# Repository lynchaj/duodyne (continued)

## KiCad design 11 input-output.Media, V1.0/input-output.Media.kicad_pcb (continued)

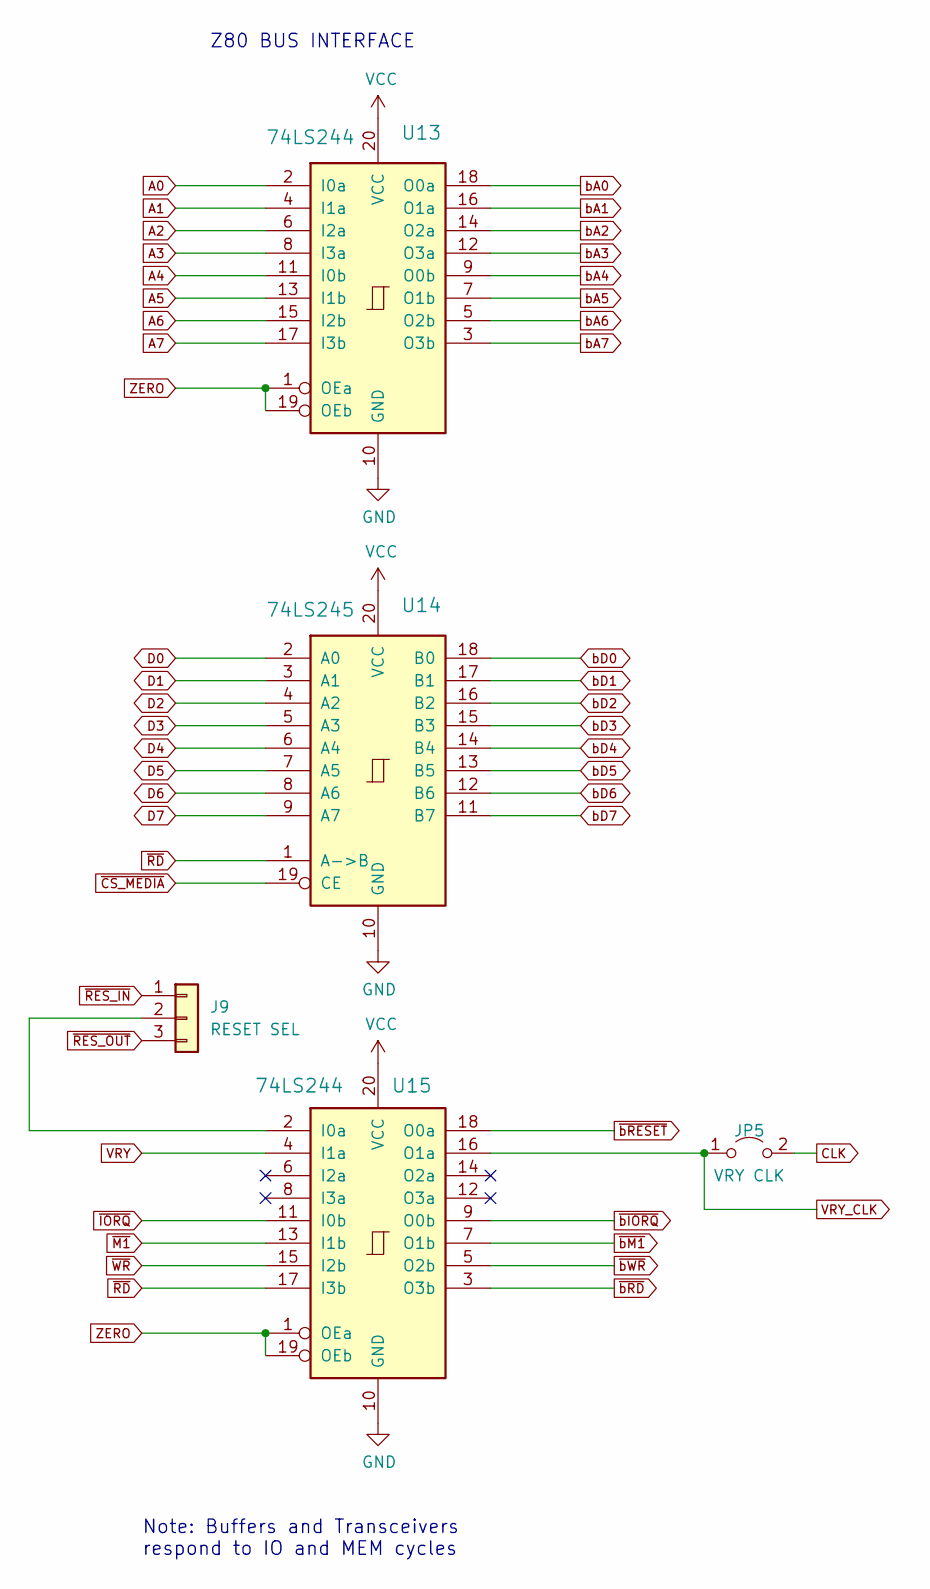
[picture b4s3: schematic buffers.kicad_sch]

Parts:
J9: RESET SEL; PinHeader_1x03_P2.54mm_Vertical
JP5: VRY CLK; PinHeader_1x02_P2.54mm_Vertical
U13, U15: 74LS244; DIP-20_W7.62mm
U14: 74LS245; DIP-20_W7.62mm

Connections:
A0: U13.2 (I0a); also elsewhere on the board
A1: U13.4 (I1a); also elsewhere on the board
A2: U13.6 (I2a); also elsewhere on the board
A3: U13.8 (I3a); also elsewhere on the board
A4: U13.11 (I0b); also elsewhere on the board
A5: U13.13 (I1b); also elsewhere on the board
A6: U13.15 (I2b); also elsewhere on the board
A7: U13.17 (I3b); also elsewhere on the board
CLK: JP5.2 (B); also elsewhere on the board
D0: U14.2 (A0); also elsewhere on the board
D1: U14.3 (A1); also elsewhere on the board
D2: U14.4 (A2); also elsewhere on the board
D3: U14.5 (A3); also elsewhere on the board
D4: U14.6 (A4); also elsewhere on the board
D5: U14.7 (A5); also elsewhere on the board
D6: U14.8 (A6); also elsewhere on the board
D7: U14.9 (A7); also elsewhere on the board
GND: U13.10 (GND), U14.10 (GND), U15.10 (GND); also elsewhere on the board
unnamed: J9.2, U15.2 (I0a)
VCC: U13.20 (VCC), U14.20 (VCC), U15.20 (VCC); also elsewhere on the board
VRY: U15.4 (I1a); also elsewhere on the board
VRY_CLK: JP5.1 (A), U15.16 (O1a); also elsewhere on the board
ZERO: U13.1 (OEa), U13.19 (OEb), U15.1 (OEa), U15.19 (OEb); also elsewhere on the board
bA0: U13.18 (O0a); also elsewhere on the board
bA1: U13.16 (O1a); also elsewhere on the board
bA2: U13.14 (O2a); also elsewhere on the board
bA3: U13.12 (O3a); also elsewhere on the board
bA4: U13.9 (O0b); also elsewhere on the board
bA5: U13.7 (O1b); also elsewhere on the board
bA6: U13.5 (O2b); also elsewhere on the board
bA7: U13.3 (O3b); also elsewhere on the board
bD0: U14.18 (B0); also elsewhere on the board
bD1: U14.17 (B1); also elsewhere on the board
bD2: U14.16 (B2); also elsewhere on the board
bD3: U14.15 (B3); also elsewhere on the board
bD4: U14.14 (B4); also elsewhere on the board
bD5: U14.13 (B5); also elsewhere on the board
bD6: U14.12 (B6); also elsewhere on the board
bD7: U14.11 (B7); also elsewhere on the board
~CS_MEDIA: U14.19 (CE); also elsewhere on the board
~IORQ: U15.11 (I0b); also elsewhere on the board
~M1: U15.13 (I1b); also elsewhere on the board
~RD: U14.1 (A->B), U15.17 (I3b); also elsewhere on the board
~RES_IN: J9.1; also elsewhere on the board
~RES_OUT: J9.3; also elsewhere on the board
~WR: U15.15 (I2b); also elsewhere on the board
~bIORQ: U15.9 (O0b); also elsewhere on the board
~bM1: U15.7 (O1b); also elsewhere on the board
~bRD: U15.3 (O3b); also elsewhere on the board
~bRESET: U15.18 (O0a); also elsewhere on the board
~bWR: U15.5 (O2b); also elsewhere on the board

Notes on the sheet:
Z80 BUS INTERFACE
Note: Buffers and Transceivers respond to IO and MEM cycles

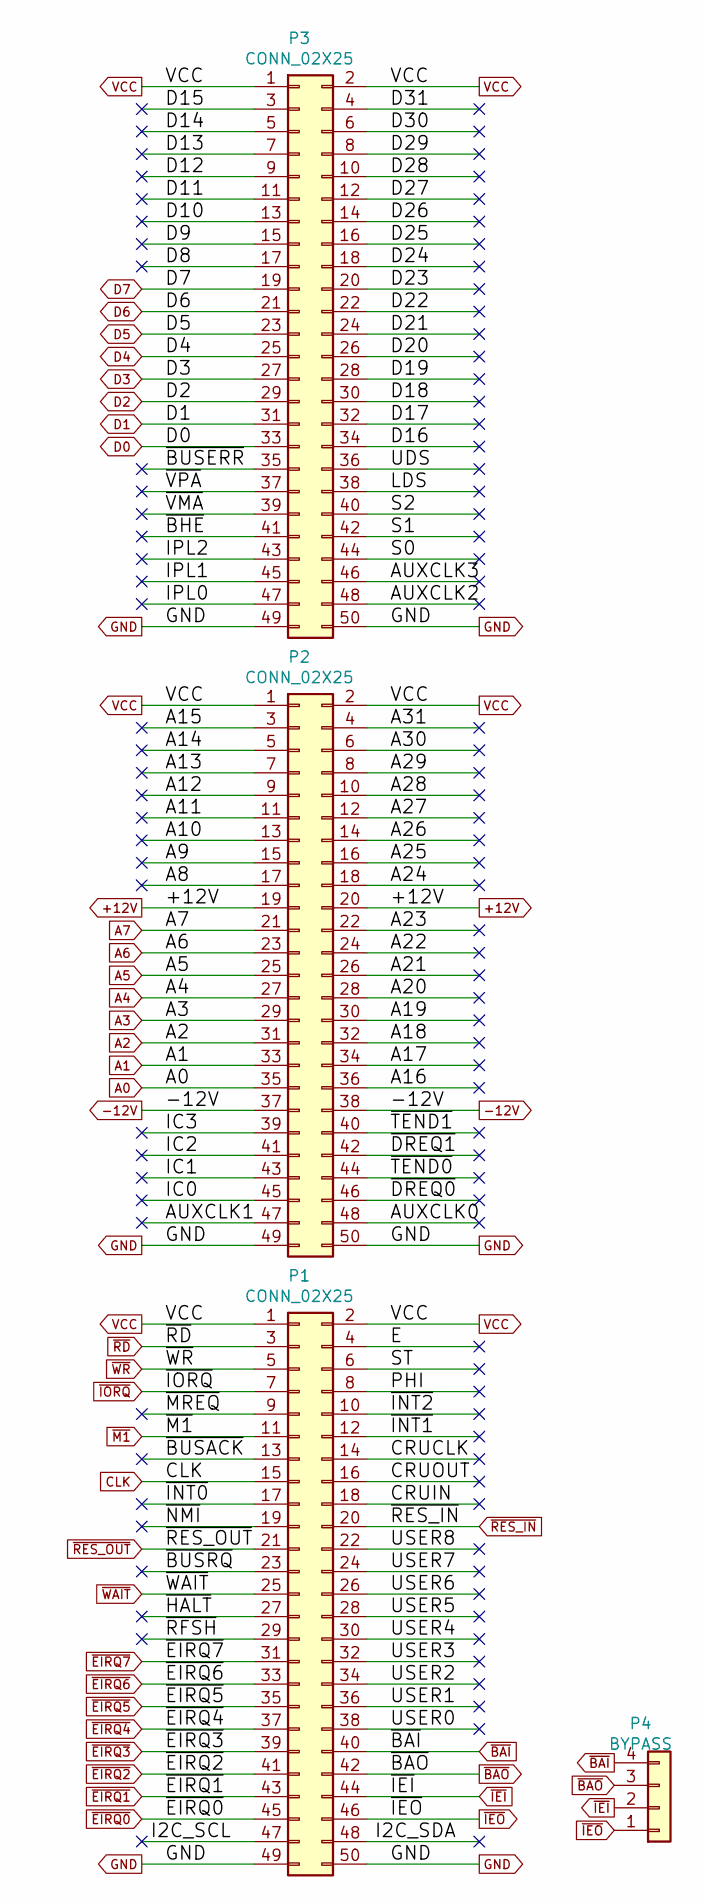
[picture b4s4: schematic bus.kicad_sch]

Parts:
P1, P2, P3: CONN_02X25; IDC-Header_2x25_P2.54mm_Horizontal
P4: BYPASS; PinHeader_1x04_P2.54mm_Vertical

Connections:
+12V: P2.19, P2.20; also elsewhere on the board
-12V: P2.37, P2.38
/bus/A8: P2.17
/bus/A9: P2.15
/bus/A10: P2.13
/bus/A11: P2.11
/bus/A12: P2.9
/bus/A13: P2.7
/bus/A14: P2.5
/bus/A15: P2.3
/bus/A16: P2.36
/bus/A17: P2.34
/bus/A18: P2.32
/bus/A19: P2.30
/bus/A20: P2.28
/bus/A21: P2.26
/bus/A22: P2.24
/bus/A23: P2.22
/bus/A24: P2.18
/bus/A25: P2.16
/bus/A26: P2.14
/bus/A27: P2.12
/bus/A28: P2.10
/bus/A29: P2.8
/bus/A30: P2.6
/bus/A31: P2.4
/bus/AUXCLK0: P2.48
/bus/AUXCLK1: P2.47
/bus/AUXCLK2: P3.48
/bus/AUXCLK3: P3.46
/bus/CRUCLK: P1.14
/bus/CRUIN: P1.18
/bus/CRUOUT: P1.16
/bus/D8: P3.17
/bus/D9: P3.15
/bus/D10: P3.13
/bus/D11: P3.11
/bus/D12: P3.9
/bus/D13: P3.7
/bus/D14: P3.5
/bus/D15: P3.3
/bus/D16: P3.34
/bus/D17: P3.32
/bus/D18: P3.30
/bus/D19: P3.28
/bus/D20: P3.26
/bus/D21: P3.24
/bus/D22: P3.22
/bus/D23: P3.20
/bus/D24: P3.18
/bus/D25: P3.16
/bus/D26: P3.14
/bus/D27: P3.12
/bus/D28: P3.10
/bus/D29: P3.8
/bus/D30: P3.6
/bus/D31: P3.4
/bus/E: P1.4
/bus/I2C_SCL: P1.47
/bus/I2C_SDA: P1.48
/bus/IC0: P2.45
/bus/IC1: P2.43
/bus/IC2: P2.41
/bus/IC3: P2.39
/bus/IPL0: P3.47
/bus/IPL1: P3.45
/bus/IPL2: P3.43
/bus/LDS: P3.38
/bus/PHI: P1.8
/bus/S0: P3.44
/bus/S1: P3.42
/bus/S2: P3.40
/bus/ST: P1.6
/bus/UDS: P3.36
/bus/USER0: P1.38
/bus/USER1: P1.36
/bus/USER2: P1.34
/bus/USER3: P1.32
/bus/USER4: P1.30
/bus/USER5: P1.28
/bus/USER6: P1.26
/bus/USER7: P1.24
/bus/USER8: P1.22
/bus/~BHE: P3.41
/bus/~BUSACK: P1.13
/bus/~BUSERR: P3.35
/bus/~BUSRQ: P1.23
/bus/~DREQ0: P2.46
/bus/~DREQ1: P2.42
/bus/~HALT: P1.27
/bus/~INT0: P1.17
/bus/~INT1: P1.12
/bus/~INT2: P1.10
/bus/~MREQ: P1.9
/bus/~NMI: P1.19
/bus/~RFSH: P1.29
/bus/~TEND0: P2.44
/bus/~TEND1: P2.40
/bus/~VMA: P3.39
/bus/~VPA: P3.37
A0: P2.35; also elsewhere on the board
A1: P2.33; also elsewhere on the board
A2: P2.31; also elsewhere on the board
A3: P2.29; also elsewhere on the board
A4: P2.27; also elsewhere on the board
A5: P2.25; also elsewhere on the board
A6: P2.23; also elsewhere on the board
A7: P2.21; also elsewhere on the board
CLK: P1.15; also elsewhere on the board
D0: P3.33; also elsewhere on the board
D1: P3.31; also elsewhere on the board
D2: P3.29; also elsewhere on the board
D3: P3.27; also elsewhere on the board
D4: P3.25; also elsewhere on the board
D5: P3.23; also elsewhere on the board
D6: P3.21; also elsewhere on the board
D7: P3.19; also elsewhere on the board
GND: P1.49, P1.50, P2.49, P2.50, P3.49, P3.50; also elsewhere on the board
VCC: P1.1, P1.2, P2.1, P2.2, P3.1, P3.2; also elsewhere on the board
~BAI: P1.40, P4.4
~BAO: P1.42, P4.3
~IEI: P1.44, P4.2
~IEO: P1.46, P4.1
~IORQ: P1.7; also elsewhere on the board
~M1: P1.11; also elsewhere on the board
~RD: P1.3; also elsewhere on the board
~RES_IN: P1.20; also elsewhere on the board
~RES_OUT: P1.21; also elsewhere on the board
~WAIT: P1.25; also elsewhere on the board
~WR: P1.5; also elsewhere on the board

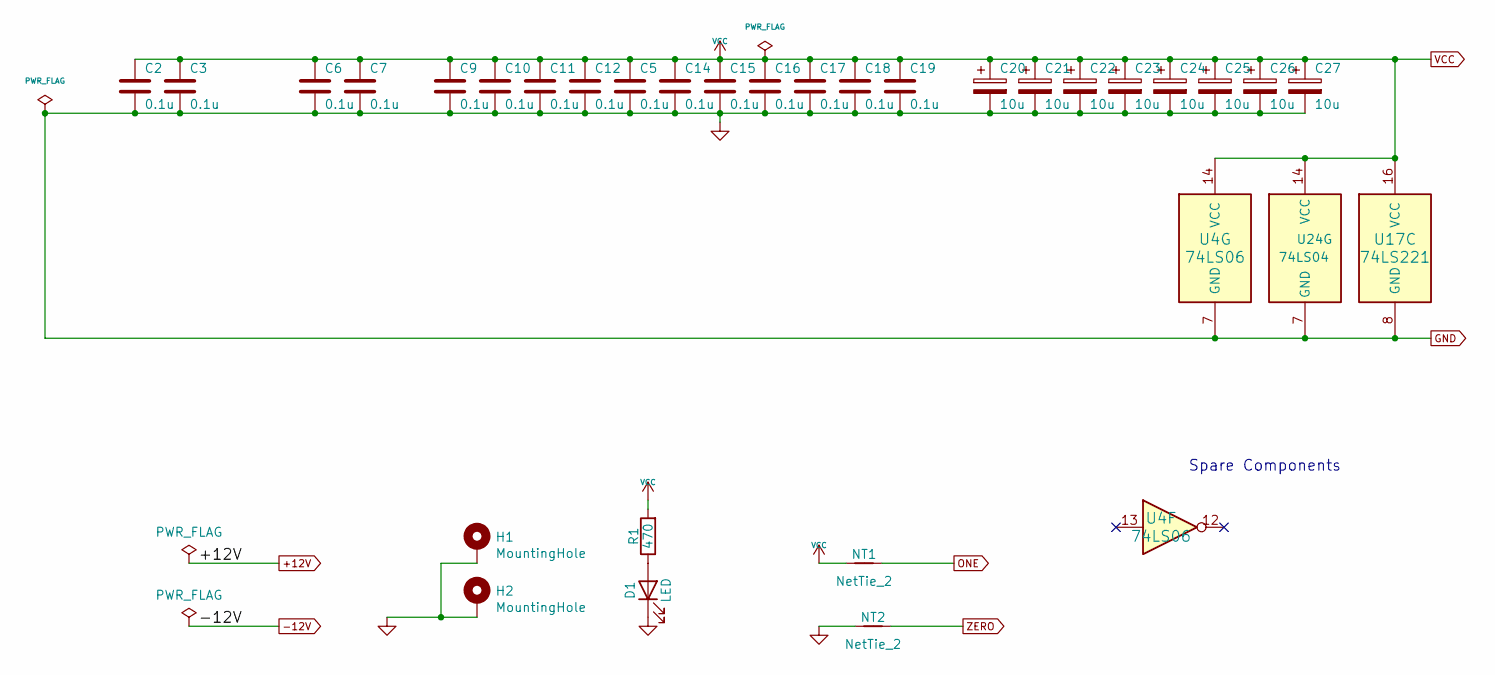
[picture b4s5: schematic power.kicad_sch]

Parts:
C2, C3, C5, C6, C7, C9, C10, C11, C12, C14, C15, C16, C17, C18, C19: 0.1u; C_Disc_D5.0mm_W2.5mm_P5.00mm
C20, C21, C22, C23, C24, C25, C26, C27: 10u; CP_Radial_D5.0mm_P2.50mm
D1: LED; LED_D3.0mm_Horizontal_O3.81mm_Z2.0mm
H1, H2: MountingHole; MountingHole_3.2mm_M3_Pad
NT1, NT2: NetTie_2; NetTie-2_THT_Pad0.3mm
R1: 470; R_Axial_DIN0207_L6.3mm_D2.5mm_P7.62mm_Horizontal
U4: 74LS06; DIP-14_W7.62mm
U17: 74LS221; DIP-16_W7.62mm
U24: 74LS04; DIP-14_W7.62mm

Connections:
GND: C2.2, C3.2, C5.2, C6.2, C7.2, C9.2, C10.2, C11.2, C12.2, C14.2, C15.2, C16.2, C17.2, C18.2, C19.2, C20.2, C21.2, C22.2, C23.2, C24.2, C25.2, C26.2, C27.2, D1.1 (K), H1.1, H2.1, NT2.1, U4.7 (GND), U17.8 (GND), U24.7 (GND); also elsewhere on the board
unnamed: D1.2 (A), R1.1
ONE: NT1.2; also elsewhere on the board
VCC: C2.1, C3.1, C5.1, C6.1, C7.1, C9.1, C10.1, C11.1, C12.1, C14.1, C15.1, C16.1, C17.1, C18.1, C19.1, C20.1, C21.1, C22.1, C23.1, C24.1, C25.1, C26.1, C27.1, NT1.1, R1.2, U4.14 (VCC), U17.16 (VCC), U24.14 (VCC); also elsewhere on the board
ZERO: NT2.2; also elsewhere on the board

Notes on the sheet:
Spare Components

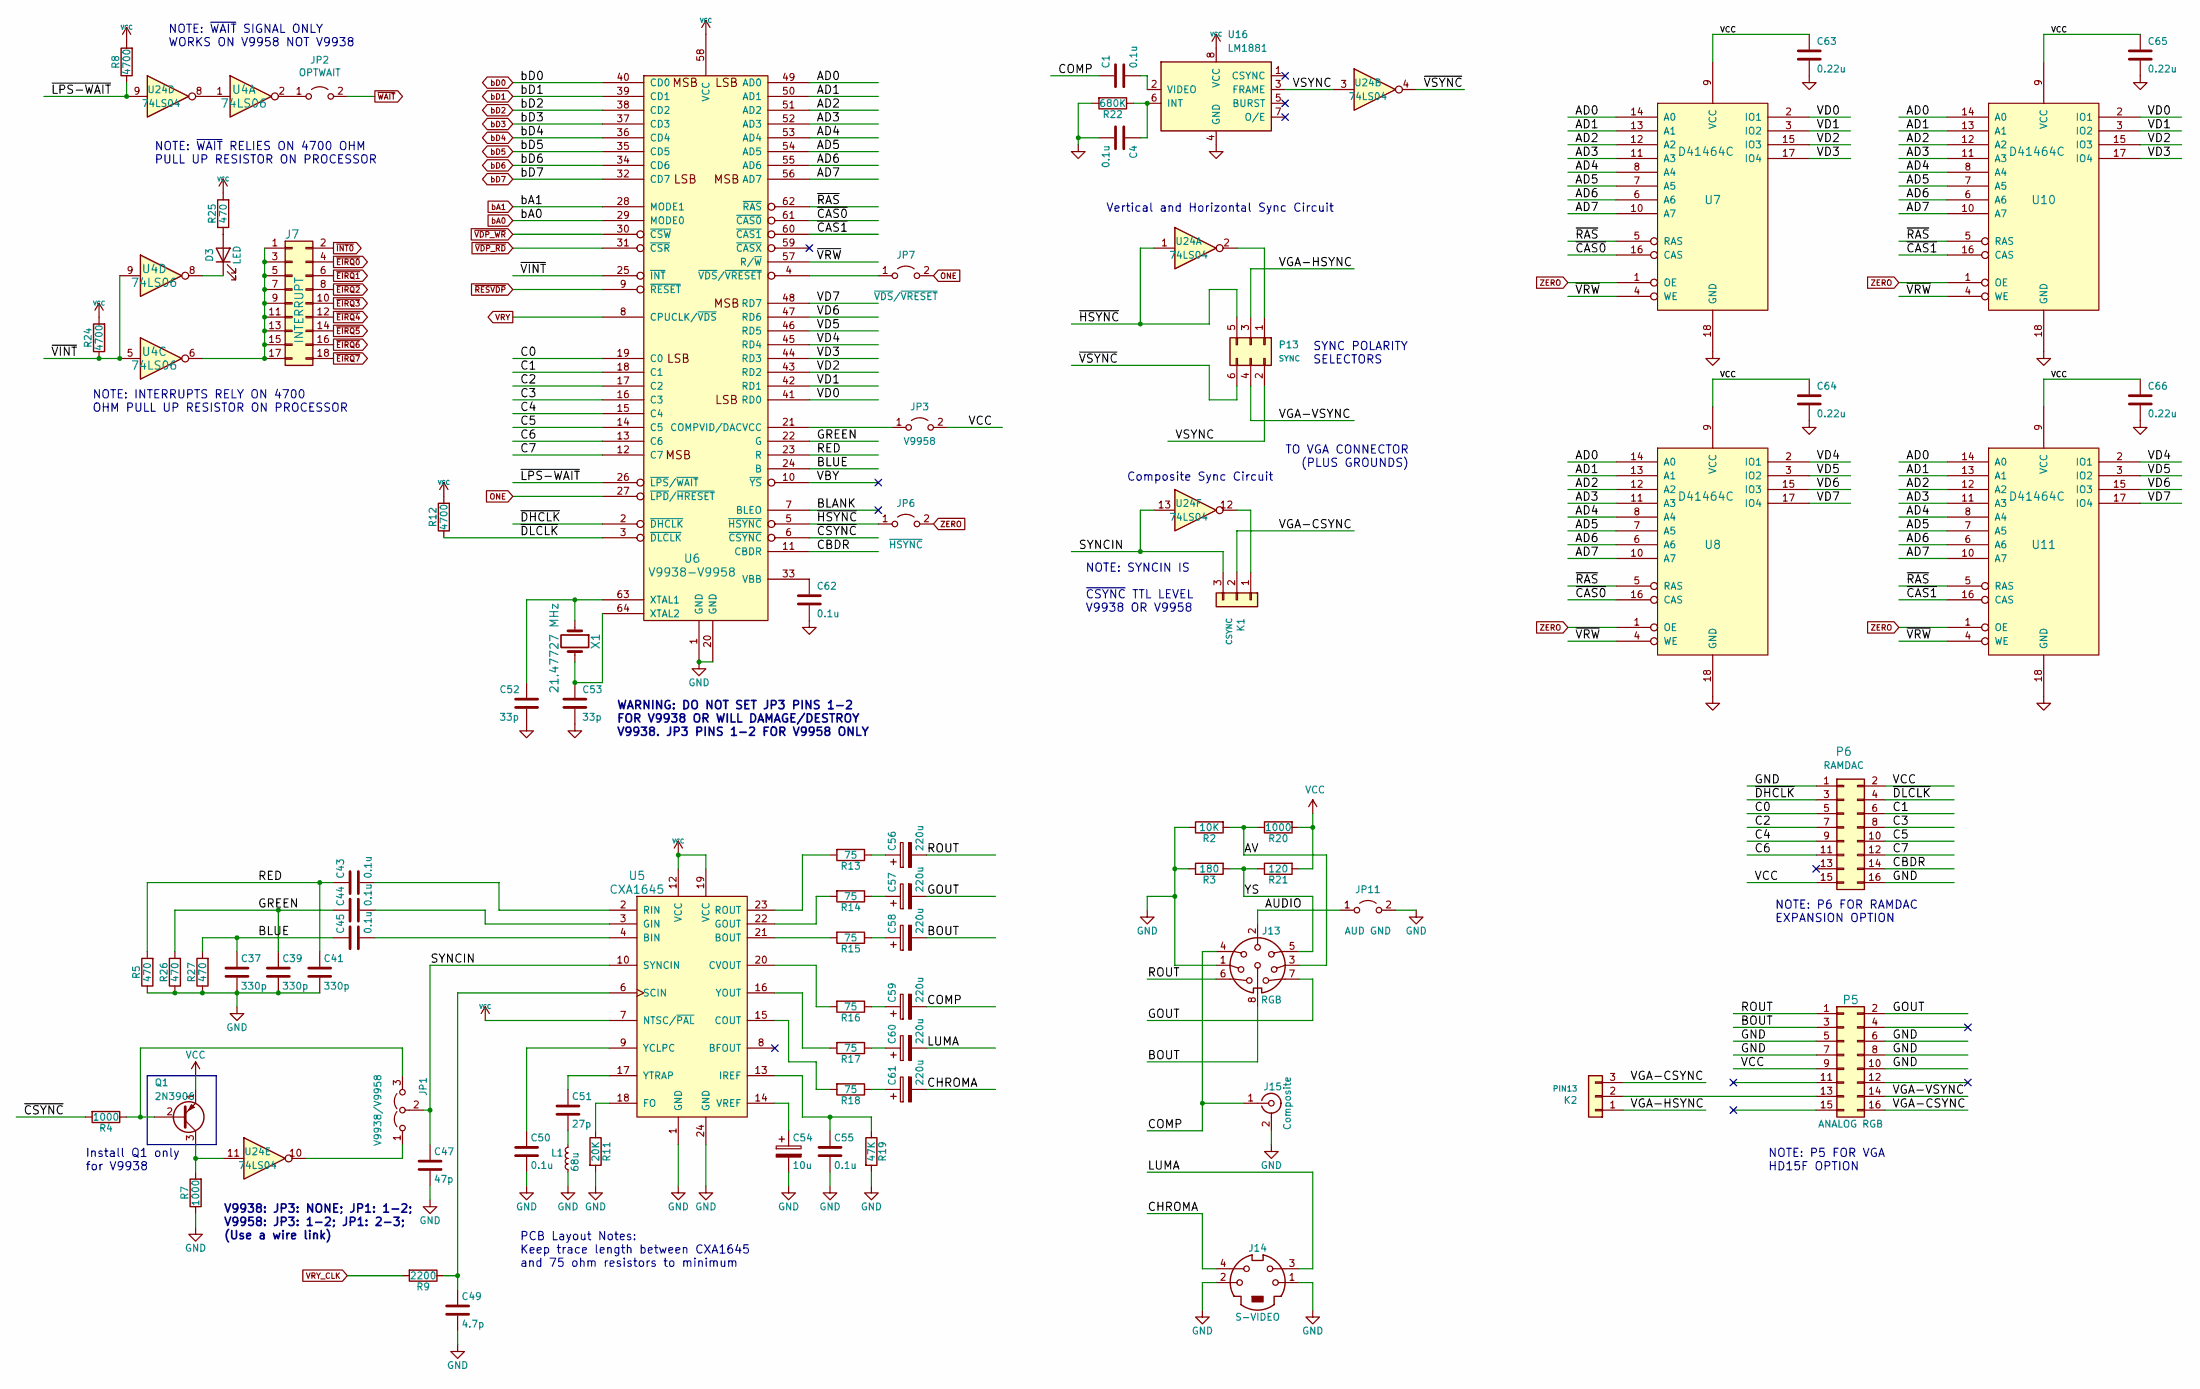
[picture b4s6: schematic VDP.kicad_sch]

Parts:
C1, C4, C43, C44, C45, C50, C55, C62: 0.1u; C_Disc_D5.0mm_W2.5mm_P5.00mm
C37, C39, C41: 330p; C_Disc_D5.0mm_W2.5mm_P5.00mm
C47: 47p; C_Disc_D5.0mm_W2.5mm_P5.00mm
C49: 4.7p; C_Disc_D5.0mm_W2.5mm_P5.00mm
C51: 27p; C_Disc_D5.0mm_W2.5mm_P5.00mm
C52, C53: 33p; C_Disc_D5.0mm_W2.5mm_P5.00mm
C54: 10u; CP_Radial_D5.0mm_P2.50mm
C56, C57, C58, C59, C60, C61: 220u; CP_Radial_D6.3mm_P2.50mm
C63, C64, C65, C66: 0.22u; C_Disc_D5.0mm_W2.5mm_P5.00mm
D3: LED; LED_D3.0mm_Horizontal_O3.81mm_Z2.0mm
J7: INTERRUPT; PinHeader_2x09_P2.54mm_Vertical
J13: RGB; Conn_DIN_8pin
J14: S-VIDEO; Conn_Mini_DIN_4pin
J15: Composite; Conn_RCA_Right
JP1: V9938/V9958; PinHeader_1x03_P2.54mm_Vertical
JP2: OPTWAIT; PinHeader_1x02_P2.54mm_Vertical
JP3: V9958; PinHeader_1x02_P2.54mm_Vertical
JP6: ~{HSYNC}; PinHeader_1x02_P2.54mm_Vertical
JP7: ~{VDS}/~{VRESET}; PinHeader_1x02_P2.54mm_Vertical
JP11: AUD GND; PinHeader_1x02_P2.54mm_Vertical
K1: CSYNC; PinHeader_1x03_P2.54mm_Vertical
K2: PIN13; PinHeader_1x03_P2.54mm_Vertical
L1: 68u; L_Axial_L6.6mm_D2.7mm_P10.16mm_Horizontal_Vishay_IM-2
P5: ANALOG RGB; PinHeader_2x08_P2.54mm_Vertical
P6: RAMDAC; PinHeader_2x08_P2.54mm_Vertical
P13: SYNC; PinHeader_2x03_P2.54mm_Vertical
Q1: 2N3906; TO-92_Inline
R2: 10K; R_Axial_DIN0207_L6.3mm_D2.5mm_P7.62mm_Horizontal
R3: 180; R_Axial_DIN0207_L6.3mm_D2.5mm_P7.62mm_Horizontal
R4, R7, R20: 1000; R_Axial_DIN0207_L6.3mm_D2.5mm_P7.62mm_Horizontal
R5, R25, R26, R27: 470; R_Axial_DIN0207_L6.3mm_D2.5mm_P7.62mm_Horizontal
R8, R12, R24: 4700; R_Axial_DIN0207_L6.3mm_D2.5mm_P7.62mm_Horizontal
R9: 2200; R_Axial_DIN0207_L6.3mm_D2.5mm_P7.62mm_Horizontal
R11: 20K; R_Axial_DIN0207_L6.3mm_D2.5mm_P7.62mm_Horizontal
R13, R14, R15, R16, R17, R18: 75; R_Axial_DIN0207_L6.3mm_D2.5mm_P7.62mm_Horizontal
R19: 47K; R_Axial_DIN0207_L6.3mm_D2.5mm_P7.62mm_Horizontal
R21: 120; R_Axial_DIN0207_L6.3mm_D2.5mm_P7.62mm_Horizontal
R22: 680K; R_Axial_DIN0207_L6.3mm_D2.5mm_P7.62mm_Horizontal
U4: 74LS06; DIP-14_W7.62mm
U5: CXA1645; DIP-24_W10.16mm
U6: V9938-V9958; renesas21-DIP64-S
U7, U8, U10, U11: D41464C; DIP-18_W7.62mm
U16: LM1881; DIP-8_W7.62mm
U24: 74LS04; DIP-14_W7.62mm
X1: 21.47727 MHz; Crystal_HC49-4H_Vertical

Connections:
/VDP/AD0: U6.49 (AD0), U7.14 (A0), U8.14 (A0), U10.14 (A0), U11.14 (A0)
/VDP/AD1: U6.50 (AD1), U7.13 (A1), U8.13 (A1), U10.13 (A1), U11.13 (A1)
/VDP/AD2: U6.51 (AD2), U7.12 (A2), U8.12 (A2), U10.12 (A2), U11.12 (A2)
/VDP/AD3: U6.52 (AD3), U7.11 (A3), U8.11 (A3), U10.11 (A3), U11.11 (A3)
/VDP/AD4: U6.53 (AD4), U7.8 (A4), U8.8 (A4), U10.8 (A4), U11.8 (A4)
/VDP/AD5: U6.54 (AD5), U7.7 (A5), U8.7 (A5), U10.7 (A5), U11.7 (A5)
/VDP/AD6: U6.55 (AD6), U7.6 (A6), U8.6 (A6), U10.6 (A6), U11.6 (A6)
/VDP/AD7: U6.56 (AD7), U7.10 (A7), U8.10 (A7), U10.10 (A7), U11.10 (A7)
/VDP/AUDIO: J13.2, JP11.1 (A)
/VDP/AV: J13.3, R2.2, R20.1
/VDP/BLANK: U6.7 (BLEO)
/VDP/BLUE: C37.1, C45.1, R27.2, U6.24 (B)
/VDP/BOUT: C58.2, J13.8, P5.3
/VDP/C0: P6.5, U6.19 (C0)
/VDP/C1: P6.6, U6.18 (C1)
/VDP/C2: P6.7, U6.17 (C2)
/VDP/C3: P6.8, U6.16 (C3)
/VDP/C4: P6.9, U6.15 (C4)
/VDP/C5: P6.10, U6.14 (C5)
/VDP/C6: P6.11, U6.13 (C6)
/VDP/C7: P6.12, U6.12 (C7)
/VDP/CBDR: P6.14, U6.11 (CBDR)
/VDP/CHROMA: C61.2, J14.4
/VDP/COMP: C1.1, C59.2, J13.4, J15.1 (In)
/VDP/GOUT: C57.2, J13.7, P5.2
/VDP/GREEN: C39.1, C44.1, R26.2, U6.22 (G)
/VDP/LUMA: C60.2, J14.3
/VDP/RED: C41.1, C43.1, R5.2, U6.23 (R)
/VDP/ROUT: C56.2, J13.6, P5.1
/VDP/SYNCIN: C47.1, JP1.2 (C), K1.3, U5.10 (SYNCIN), U24.13
/VDP/VBY: U6.10 (~YS)
/VDP/VD0: U6.41 (RD0), U7.2 (IO1), U10.2 (IO1)
/VDP/VD1: U6.42 (RD1), U7.3 (IO2), U10.3 (IO2)
/VDP/VD2: U6.43 (RD2), U7.15 (IO3), U10.15 (IO3)
/VDP/VD3: U6.44 (RD3), U7.17 (IO4), U10.17 (IO4)
/VDP/VD4: U6.45 (RD4), U8.2 (IO1), U11.2 (IO1)
/VDP/VD5: U6.46 (RD5), U8.3 (IO2), U11.3 (IO2)
/VDP/VD6: U6.47 (RD6), U8.15 (IO3), U11.15 (IO3)
/VDP/VD7: U6.48 (RD7), U8.17 (IO4), U11.17 (IO4)
/VDP/VGA-CSYNC: K1.2, K2.3, P5.16
/VDP/VGA-HSYNC: K2.1, P13.3
/VDP/VGA-VSYNC: P5.14, P13.4
/VDP/VSYNC: P13.2, U16.3 (FRAME), U24.3
/VDP/YS: J13.5, R3.2, R21.1
/VDP/~CAS0: U6.61 (~CAS0), U7.16 (CAS), U8.16 (CAS)
/VDP/~CAS1: U6.60 (~CAS1), U10.16 (CAS), U11.16 (CAS)
/VDP/~CSYNC: R4.2, U6.6 (~CSYNC)
/VDP/~DHCLK: P6.3, U6.2 (~DHCLK)
/VDP/~DLCLK: P6.4, R12.1, U6.3 (~DLCLK)
/VDP/~HSYNC: JP6.1 (A), P13.5, U6.5 (~HSYNC), U24.1
/VDP/~LPS-WAIT: R8.1, U6.26 (~LPS/~WAIT), U24.9
/VDP/~RAS: U6.62 (~RAS), U7.5 (RAS), U8.5 (RAS), U10.5 (RAS), U11.5 (RAS)
/VDP/~VINT: R24.1, U4.5, U4.9, U6.25 (~INT)
/VDP/~VRW: U6.57 (R/~W), U7.4 (WE), U8.4 (WE), U10.4 (WE), U11.4 (WE)
/VDP/~VSYNC: P13.6, U24.4
GND: C4.2, C37.2, C39.2, C41.2, C47.2, C49.2, C50.2, C52.2, C53.2, C54.2, C55.2, C62.2, C63.2, C64.2, C65.2, C66.2, J13.1, J14.1, J14.2, J15.2 (Ext), JP11.2 (B), L1.2, P5.5, P5.6, P5.7, P5.8, P5.10, P6.1, P6.16, R2.1, R3.1, R5.1, R7.1, R11.2, R19.2, R22.2, R26.1, R27.1, U5.1 (GND), U5.24 (GND), U6.1 (GND), U6.20 (GND), U7.18 (GND), U8.18 (GND), U10.18 (GND), U11.18 (GND), U16.4 (GND); also elsewhere on the board
unnamed: C1.2, U16.2 (VIDEO)
unnamed: C4.1, R22.1, U16.6 (INT)
unnamed: C43.2, U5.2 (RIN)
unnamed: C44.2, U5.3 (GIN)
unnamed: C45.2, U5.4 (BIN)
unnamed: C49.1, R9.1, U5.6 (SCIN)
unnamed: C50.1, U5.9 (YCLPC)
unnamed: C51.1, U5.17 (YTRAP)
unnamed: C51.2, L1.1
unnamed: C52.1, U6.63 (XTAL1), X1.1
unnamed: C53.1, U6.64 (XTAL2), X1.2
unnamed: C54.1, U5.14 (VREF)
unnamed: C55.1, R19.1, U5.13 (IREF)
unnamed: C56.1, R13.1
unnamed: C57.1, R14.1
unnamed: C58.1, R15.1
unnamed: C59.1, R16.1
unnamed: C60.1, R17.1
unnamed: C61.1, R18.1
unnamed: C62.1, U6.33 (VBB)
unnamed: D3.1 (K), U4.8
unnamed: D3.2 (A), R25.1
unnamed: J7.1, J7.3, J7.5, J7.7, J7.9, J7.11, J7.13, J7.15, J7.17, U4.6
unnamed: JP1.1 (A), U24.10
unnamed: JP1.3 (B), Q1.2 (B), R4.1
unnamed: JP2.1 (A), U4.2
unnamed: JP3.1 (A), U6.21 (COMPVID/DACVCC)
unnamed: JP7.1 (A), U6.4 (~VDS/~VRESET)
unnamed: K1.1, U24.12
unnamed: K2.2, P5.13
unnamed: P13.1, U24.2
unnamed: Q1.3 (C), R7.2, U24.11
unnamed: R11.1, U5.18 (FO)
unnamed: R13.2, U5.23 (ROUT)
unnamed: R14.2, U5.22 (GOUT)
unnamed: R15.2, U5.21 (BOUT)
unnamed: R16.2, U5.20 (CVOUT)
unnamed: R17.2, U5.16 (YOUT)
unnamed: R18.2, U5.15 (COUT)
unnamed: U4.1, U24.8
ONE: JP7.2 (B), U6.27 (~LPD/~HRESET); also elsewhere on the board
VCC: C63.1, C64.1, C65.1, C66.1, JP3.2 (B), P5.9, P6.2, P6.15, Q1.1 (E), R8.2, R12.2, R20.2, R21.2, R24.2, R25.2, U5.7 (NTSC/~PAL), U5.12 (VCC), U5.19 (VCC), U6.58 (VCC), U7.9 (VCC), U8.9 (VCC), U10.9 (VCC), U11.9 (VCC), U16.8 (VCC); also elsewhere on the board
VRY: U6.8 (CPUCLK/~VDS); also elsewhere on the board
VRY_CLK: R9.2; also elsewhere on the board
ZERO: JP6.2 (B), U7.1 (OE), U8.1 (OE), U10.1 (OE), U11.1 (OE); also elsewhere on the board
bA0: U6.29 (MODE0); also elsewhere on the board
bA1: U6.28 (MODE1); also elsewhere on the board
bD0: U6.40 (CD0); also elsewhere on the board
bD1: U6.39 (CD1); also elsewhere on the board
bD2: U6.38 (CD2); also elsewhere on the board
bD3: U6.37 (CD3); also elsewhere on the board
bD4: U6.36 (CD4); also elsewhere on the board
bD5: U6.35 (CD5); also elsewhere on the board
bD6: U6.34 (CD6); also elsewhere on the board
bD7: U6.32 (CD7); also elsewhere on the board
~RESVDP: U6.9 (~RESET); also elsewhere on the board
~VDP_RD: U6.31 (~CSR); also elsewhere on the board
~VDP_WR: U6.30 (~CSW); also elsewhere on the board
~WAIT: JP2.2 (B); also elsewhere on the board

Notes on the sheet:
PCB Layout Notes: Keep trace length between CXA1645 and 75 ohm resistors to minimum
NOTE: INTERRUPTS RELY ON 4700 OHM PULL UP RESISTOR ON PROCESSOR
Composite Sync Circuit
V9938: JP3: NONE; JP1: 1-2; V9958: JP3: 1-2; JP1: 2-3; (Use a wire link)
WARNING: DO NOT SET JP3 PINS 1-2 FOR V9938 OR WILL DAMAGE/DESTROY V9938. JP3 PINS 1-2 FOR V9958 ONLY
NOTE: ~{WAIT} SIGNAL ONLY WORKS ON V9958 NOT V9938
NOTE: ~{WAIT} RELIES ON 4700 OHM PULL UP RESISTOR ON PROCESSOR
TO VGA CONNECTOR (PLUS GROUNDS)
Vertical and Horizontal Sync Circuit
NOTE: P5 FOR VGA HD15F OPTION
Install Q1 only for V9938
NOTE: P6 FOR RAMDAC EXPANSION OPTION
SYNC POLARITY SELECTORS
NOTE: SYNCIN IS ~{CSYNC} TTL LEVEL V9938 OR V9958

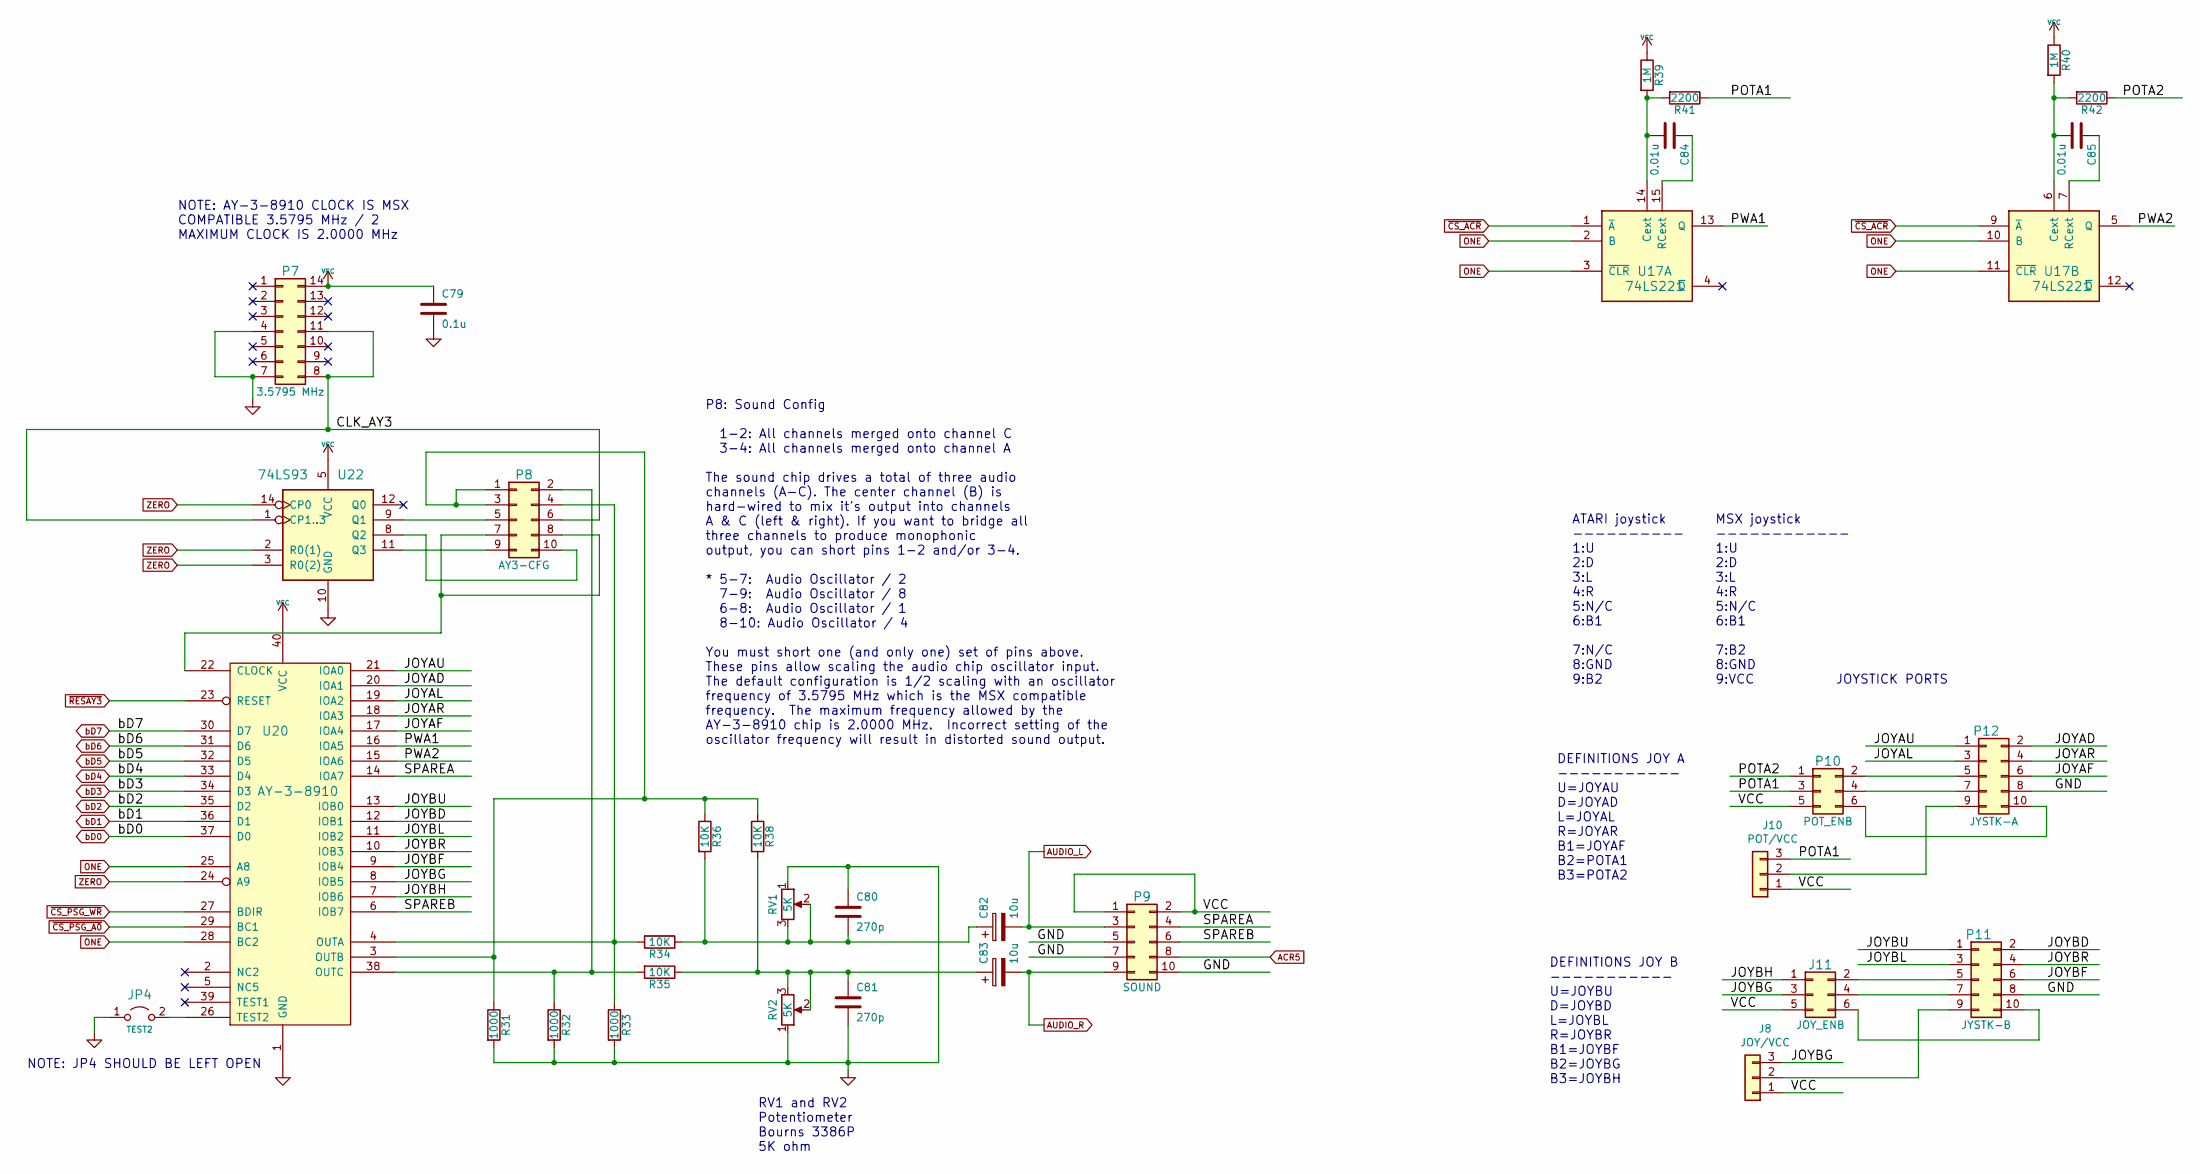
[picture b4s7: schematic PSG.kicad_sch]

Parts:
C79: 0.1u; C_Disc_D5.0mm_W2.5mm_P5.00mm
C80, C81: 270p; C_Disc_D5.0mm_W2.5mm_P5.00mm
C82, C83: 10u; CP_Radial_D5.0mm_P2.50mm
C84, C85: 0.01u; C_Disc_D5.0mm_W2.5mm_P5.00mm
J8: JOY/VCC; PinHeader_1x03_P2.54mm_Vertical
J10: POT/VCC; PinHeader_1x03_P2.54mm_Vertical
J11: JOY_ENB; PinHeader_2x03_P2.54mm_Vertical
JP4: TEST2; PinHeader_1x02_P2.54mm_Vertical
P7: 3.5795 MHz; DIP-14_W7.62mm
P8: AY3-CFG; PinHeader_2x05_P2.54mm_Vertical
P9: SOUND; IDC-Header_2x05_P2.54mm_Horizontal
P10: POT_ENB; PinHeader_2x03_P2.54mm_Vertical
P11: JYSTK-B; IDC-Header_2x05_P2.54mm_Horizontal
P12: JYSTK-A; IDC-Header_2x05_P2.54mm_Horizontal
R31, R32, R33: 1000; R_Axial_DIN0207_L6.3mm_D2.5mm_P7.62mm_Horizontal
R34, R35, R36, R38: 10K; R_Axial_DIN0207_L6.3mm_D2.5mm_P7.62mm_Horizontal
R39, R40: 1M; R_Axial_DIN0207_L6.3mm_D2.5mm_P7.62mm_Horizontal
R41, R42: 2200; R_Axial_DIN0207_L6.3mm_D2.5mm_P7.62mm_Horizontal
RV1, RV2: 5K; Potentiometer_Bourns_3386P_Vertical
U17: 74LS221; DIP-16_W7.62mm
U20: AY-3-8910; DIP-40_W15.24mm
U22: 74LS93; DIP-14_W7.62mm

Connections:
/PSG/CLK_AY3: P7.8, P7.11, P8.6, U22.1 (CP1..3)
/PSG/JOYAD: P12.2, U20.20 (IOA1)
/PSG/JOYAF: P12.6, U20.17 (IOA4)
/PSG/JOYAL: P12.3, U20.19 (IOA2)
/PSG/JOYAR: P12.4, U20.18 (IOA3)
/PSG/JOYAU: P12.1, U20.21 (IOA0)
/PSG/JOYBD: P11.2, U20.12 (IOB1)
/PSG/JOYBF: P11.6, U20.9 (IOB4)
/PSG/JOYBG: J8.3, J11.3, U20.8 (IOB5)
/PSG/JOYBH: J11.1, U20.7 (IOB6)
/PSG/JOYBL: P11.3, U20.11 (IOB2)
/PSG/JOYBR: P11.4, U20.10 (IOB3)
/PSG/JOYBU: P11.1, U20.13 (IOB0)
/PSG/POTA1: J10.3, P10.3, R41.1
/PSG/POTA2: P10.1, R42.1
/PSG/PWA1: U17.13 (Q), U20.16 (IOA5)
/PSG/PWA2: U17.5 (Q), U20.15 (IOA6)
/PSG/SPAREA: P9.4, U20.14 (IOA7)
/PSG/SPAREB: P9.6, U20.6 (IOB7)
ACR5: P9.8; also elsewhere on the board
AUDIO_L: C82.2, P9.3; also elsewhere on the board
AUDIO_R: C83.2, P9.9; also elsewhere on the board
GND: C79.2, C80.1, C81.2, JP4.1 (A), P7.4, P7.7, P9.5, P9.7, P9.10, P11.8, P12.8, R31.2, R32.2, R33.2, RV1.1, RV2.1, U20.1 (GND), U22.10 (GND); also elsewhere on the board
unnamed: C80.2, C82.1, R34.1, R36.2, RV1.2, RV1.3
unnamed: C81.1, C83.1, R35.1, R38.2, RV2.2, RV2.3
unnamed: C84.1, U17.15 (RCext)
unnamed: C84.2, R39.2, R41.2, U17.14 (Cext)
unnamed: C85.1, U17.7 (RCext)
unnamed: C85.2, R40.2, R42.2, U17.6 (Cext)
unnamed: J8.2, P11.9
unnamed: J10.2, P12.9
unnamed: J11.2, P11.5
unnamed: J11.4, P11.7
unnamed: J11.6, P11.10
unnamed: JP4.2 (B), U20.26 (TEST2)
unnamed: P8.1, P8.3, R31.1, R36.1, R38.1, U20.3 (OUTB)
unnamed: P8.2, R32.1, R35.2, U20.38 (OUTC)
unnamed: P8.4, R33.1, R34.2, U20.4 (OUTA)
unnamed: P8.5, U22.9 (Q1)
unnamed: P8.7, P8.8, U20.22 (CLOCK)
unnamed: P8.9, U22.11 (Q3)
unnamed: P8.10, U22.8 (Q2)
unnamed: P10.2, P12.5
unnamed: P10.4, P12.7
unnamed: P10.6, P12.10
ONE: U17.2 (B), U17.3 (~CLR), U17.10 (B), U17.11 (~CLR), U20.25 (A8), U20.28 (BC2); also elsewhere on the board
VCC: C79.1, J8.1, J10.1, J11.5, P7.14, P9.1, P9.2, P10.5, R39.1, R40.1, U20.40 (VCC), U22.5 (VCC); also elsewhere on the board
ZERO: U20.24 (A9), U22.2 (R0(1)), U22.3 (R0(2)), U22.14 (CP0); also elsewhere on the board
bD0: U20.37 (D0); also elsewhere on the board
bD1: U20.36 (D1); also elsewhere on the board
bD2: U20.35 (D2); also elsewhere on the board
bD3: U20.34 (D3); also elsewhere on the board
bD4: U20.33 (D4); also elsewhere on the board
bD5: U20.32 (D5); also elsewhere on the board
bD6: U20.31 (D6); also elsewhere on the board
bD7: U20.30 (D7); also elsewhere on the board
~CS_ACR: U17.1 (~A), U17.9 (~A); also elsewhere on the board
~CS_PSG_A0: U20.29 (BC1); also elsewhere on the board
~CS_PSG_WR: U20.27 (BDIR); also elsewhere on the board
~RESAY3: U20.23 (RESET); also elsewhere on the board

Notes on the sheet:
RV1 and RV2 Potentiometer Bourns 3386P 5K ohm
P8: Sound Config 1-2: All channels merged onto channel C 3-4: All channels merged onto channel A The sound chip drives a total of three audio channels (A-C). The center channel (B) is hard-wired to mix it's output into channels A & C (left & right). If you want to bridge all three channels to produ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
ATARI joystick ---------- 1:U 2:D 3:L 4:R 5:N/C 6:B1 7:N/C 8:GND 9:B2
NOTE: AY-3-8910 CLOCK IS MSX COMPATIBLE 3.5795 MHz / 2 MAXIMUM CLOCK IS 2.0000 MHz
NOTE: JP4 SHOULD BE LEFT OPEN
JOYSTICK PORTS
DEFINITIONS JOY B ----------- U=JOYBU D=JOYBD L=JOYBL R=JOYBR B1=JOYBF B2=JOYBG B3=JOYBH
DEFINITIONS JOY A ----------- U=JOYAU D=JOYAD L=JOYAL R=JOYAR B1=JOYAF B2=POTA1 B3=POTA2
MSX joystick ------------ 1:U 2:D 3:L 4:R 5:N/C 6:B1 7:B2 8:GND 9:VCC
